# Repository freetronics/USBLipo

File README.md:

Freetronics USBLipo is an OSHW smart charger for 3.7V LiPo cells: just
plug in your cell and a USB power source such as a mobile phone
charger or computer, and you're done.

For more details see [the USBLipo home page](http://www.freetronics.com.au/products/usb-lipo-charger).

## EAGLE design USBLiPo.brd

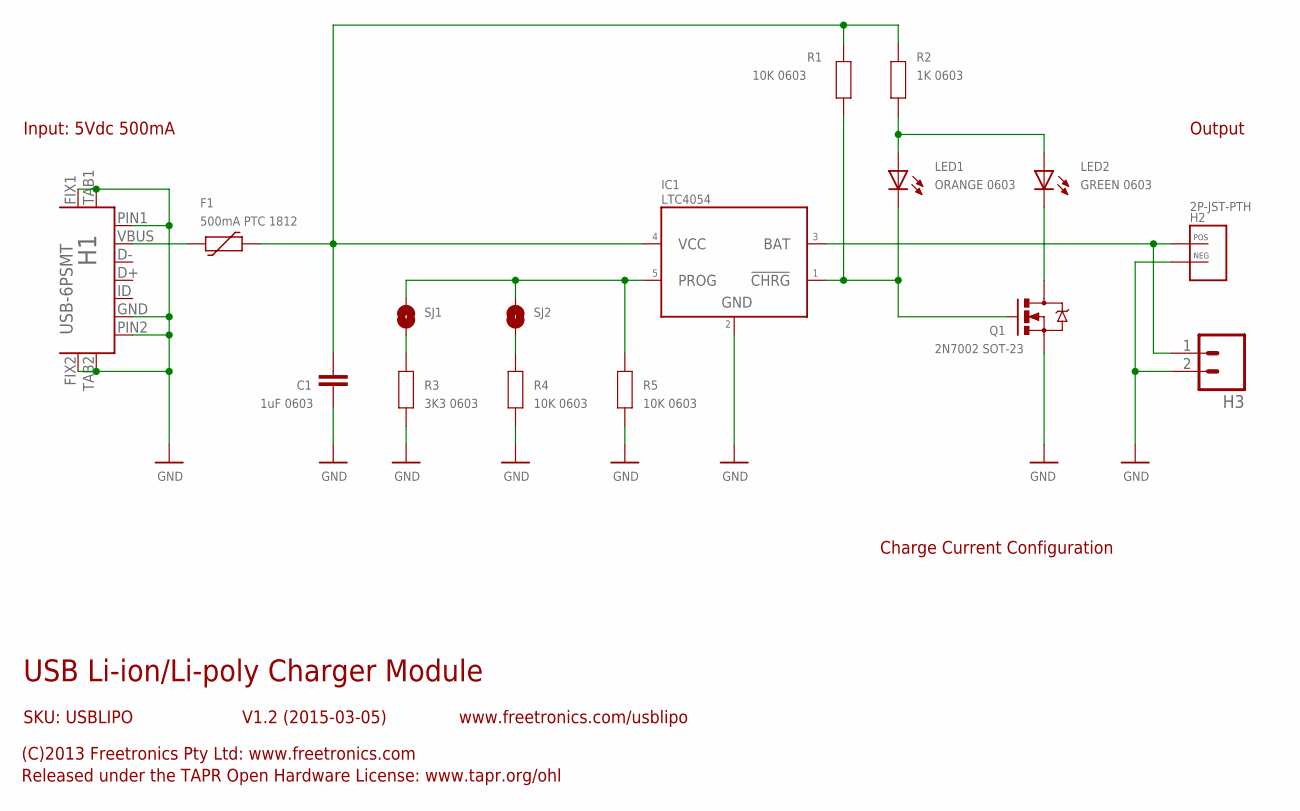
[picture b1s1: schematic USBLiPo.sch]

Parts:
C1: 1uF 0603; 0603
F1: 500mA PTC 1812; 1812
H1: USB-6PSMT; USB-MICROB-MB05PMXX
H2: 2P-JST-PTH; JST-2MM-TH-RA
H3: M02PTH; 1X02
IC1: LTC4054; SOT23-5
LED1: ORANGE 0603; LED-0603
LED2: GREEN 0603; LED-0603
Q1: 2N7002 SOT-23; SOT23-3
R1, R4, R5: 10K 0603; 0603
R2: 1K 0603; 0603
R3: 3K3 0603; 0603
SJ1, SJ2: SJ

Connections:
GND: C1.1, H1.FIX1, H1.FIX2, H1.GND, H1.PIN1, H1.PIN2, H1.TAB1, H1.TAB2, H2.NEG, H3.2, IC1.2 (GND), Q1.2 (S), R3.2, R4.2, R5.2
unnamed: LED2.C, Q1.3 (D)
unnamed: C1.2, F1.2, IC1.4 (VCC), R1.1, R2.1
unnamed: IC1.5 (PROG), R5.1, SJ1.2, SJ2.2
unnamed: H2.POS, H3.1, IC1.3 (BAT)
unnamed: R3.1, SJ1.1
unnamed: IC1.1 (!CHRG), LED1.C, Q1.1 (G), R1.2
unnamed: R4.1, SJ2.1
unnamed: LED1.A, LED2.A, R2.2
unnamed: F1.1, H1.VBUS

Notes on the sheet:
USB Li-ion/Li-poly Charger Module
V1.2 (2015-03-05)
SKU: USBLIPO
(C)2013 Freetronics Pty Ltd: www.freetronics.com
Released under the TAPR Open Hardware License: www.tapr.org/ohl
www.freetronics.com/usblipo
Charge Current Configuration
Input: 5Vdc 500mA
Output

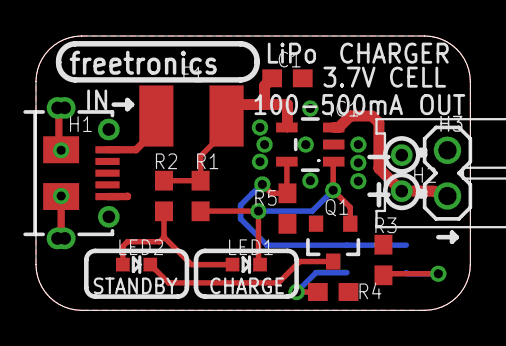
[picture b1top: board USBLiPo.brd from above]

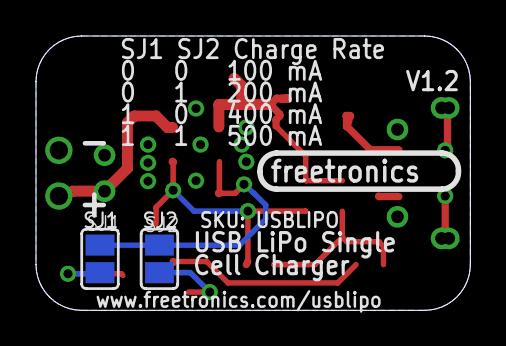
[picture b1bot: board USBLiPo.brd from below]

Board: 2 copper layers, 24.1 x 15.2 mm, 16 parts (2 on the bottom side), 10 nets.

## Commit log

2012-05-12 fixed charge current program
2012-05-15 changed JST connector to through-hole right angle
2012-07-01 Layout and overlay
2012-07-01 Removed obsolete files
2012-07-01 Overlay and values
2013-02-12 Routing improvements
2013-04-07 Final changes for v1.0 release
2013-04-07 Removed obsolete gerbers
2013-05-14 Changed USB socket to strong footprint; added 0.1 battery connector
2013-05-15 Switched pads to bottom; shorter board; ready for v1.1 release
2015-03-05 Add schematic PDF
2015-03-05 Add copy of license text
2015-03-05 Add simple README
2015-03-05 Fix silkscreen error, one charge current setting was wrong Bump version to 1.2.
